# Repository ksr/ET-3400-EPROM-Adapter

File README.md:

# ET-3400-EPROM-Adapter

Adapter to replace original ROM in ET-3400 with a standard 2716 or 2732 EPROM

Using jumpers EPROM can be enabled in 1K blocks

USE V1.1

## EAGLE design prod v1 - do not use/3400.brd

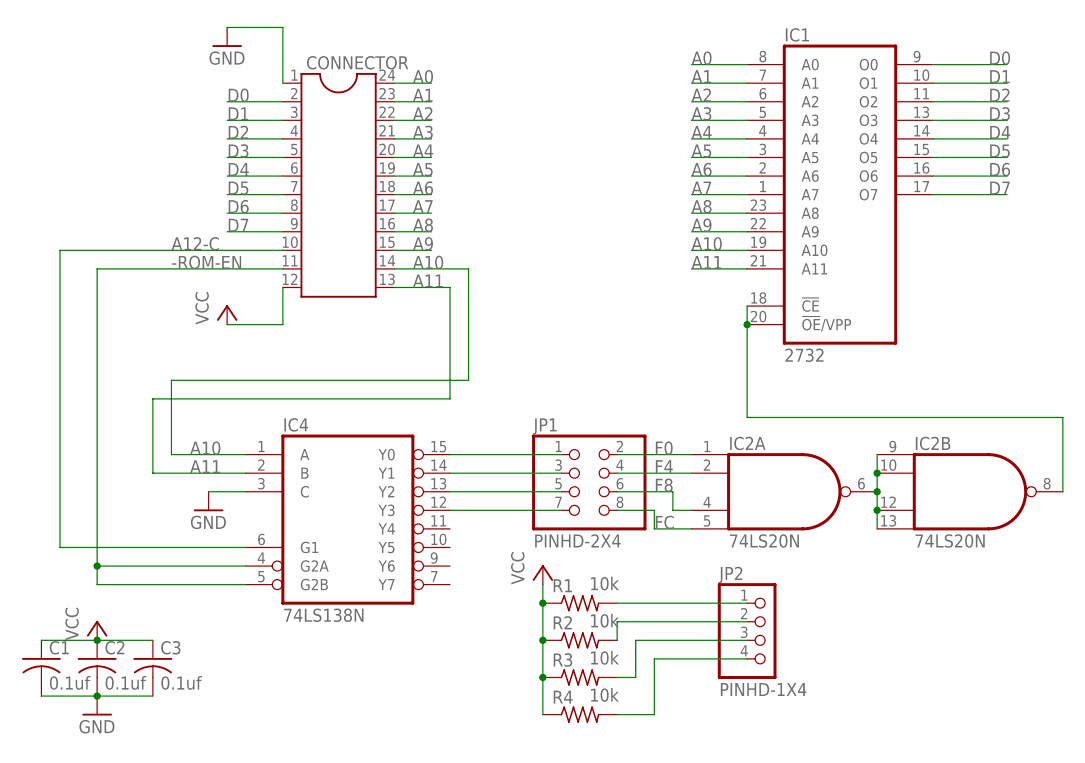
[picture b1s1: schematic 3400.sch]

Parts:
C1, C2, C3: 0.1uf; C025-024X044
CONNECTOR: DIL24-6
IC1: 2732; DIL24
IC2: 74LS20N; DIL14
IC4: 74LS138N; DIL16
JP1: PINHD-2X4; 2X04
JP2: PINHD-1X4; 1X04
R1, R2, R3, R4: 10k; 0207/10

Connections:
-ROM-EN: CONNECTOR.11, IC4.4 (G2A), IC4.5 (G2B)
A0: CONNECTOR.24, IC1.8 (A0)
A1: CONNECTOR.23, IC1.7 (A1)
A2: CONNECTOR.22, IC1.6 (A2)
A3: CONNECTOR.21, IC1.5 (A3)
A4: CONNECTOR.20, IC1.4 (A4)
A5: CONNECTOR.19, IC1.3 (A5)
A6: CONNECTOR.18, IC1.2 (A6)
A7: CONNECTOR.17, IC1.1 (A7)
A8: CONNECTOR.16, IC1.23 (A8)
A9: CONNECTOR.15, IC1.22 (A9)
A10: CONNECTOR.14, IC1.19 (A10), IC4.1 (A)
A11: CONNECTOR.13, IC1.21 (A11), IC4.2 (B)
A12-C: CONNECTOR.10, IC4.6 (G1)
D0: CONNECTOR.2, IC1.9 (O0)
D1: CONNECTOR.3, IC1.10 (O1)
D2: CONNECTOR.4, IC1.11 (O2)
D3: CONNECTOR.5, IC1.13 (O3)
D4: CONNECTOR.6, IC1.14 (O4)
D5: CONNECTOR.7, IC1.15 (O5)
D6: CONNECTOR.8, IC1.16 (O6)
D7: CONNECTOR.9, IC1.17 (O7)
F0: IC2.1 (I0), JP1.2
F4: IC2.2 (I1), JP1.4
F8: IC2.4 (I2), JP1.6
FC: IC2.5 (I3), JP1.8
GND: C1.2, C2.2, C3.2, CONNECTOR.1, IC1.12 (GND), IC2.7 (GND), IC4.3 (C), IC4.8 (GND)
unnamed: IC1.18 (!CE), IC1.20 (!OE!/VPP), IC2.8 (O)
unnamed: IC4.15 (Y0), JP1.1
unnamed: IC2.6 (O), IC2.9 (I0), IC2.10 (I1), IC2.12 (I2), IC2.13 (I3)
unnamed: IC4.14 (Y1), JP1.3
unnamed: IC4.13 (Y2), JP1.5
unnamed: IC4.12 (Y3), JP1.7
unnamed: JP2.1, R1.2
unnamed: JP2.2, R2.2
unnamed: JP2.3, R3.2
unnamed: JP2.4, R4.2
VCC: C1.1, C2.1, C3.1, CONNECTOR.12, IC1.24 (VCC), IC2.14 (VCC), IC4.16 (VCC), R1.1, R2.1, R3.1, R4.1

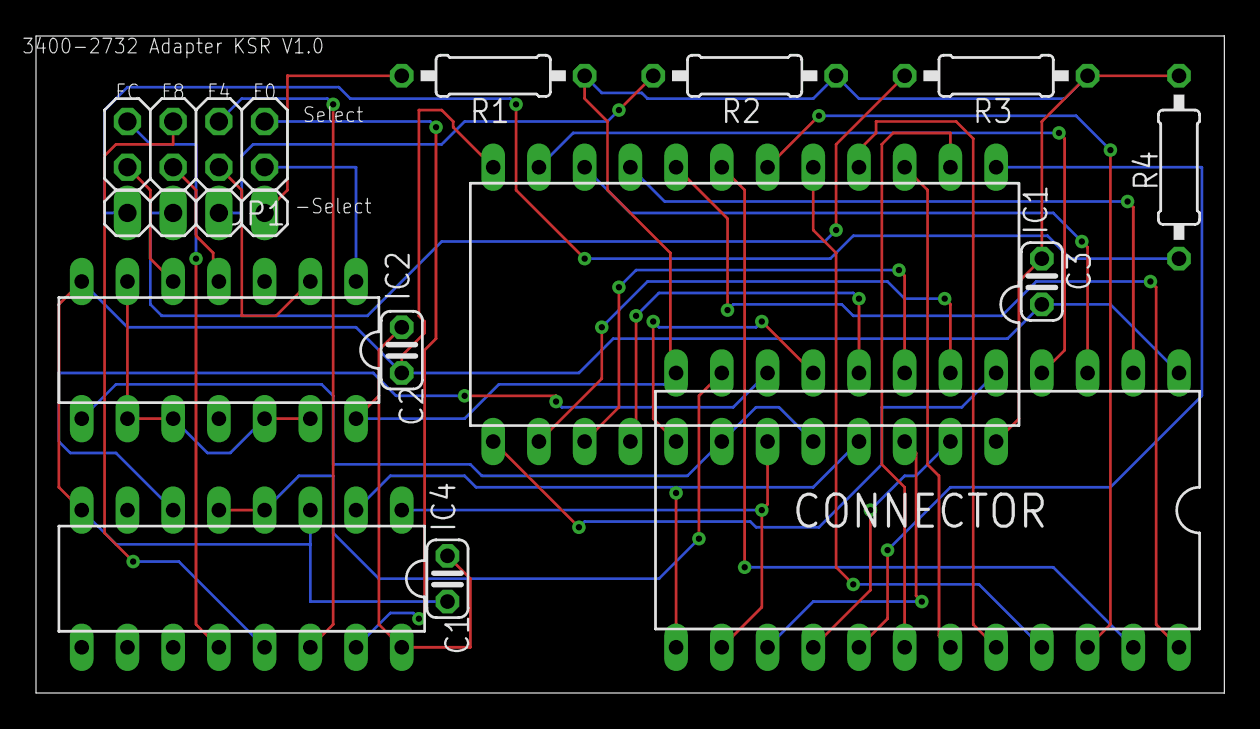
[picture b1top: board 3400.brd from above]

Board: 2 copper layers, 66.0 x 36.5 mm, 13 parts (0 on the bottom side), 38 nets.

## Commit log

2020-12-26 Initial Checkin - USE V1.1
2020-12-26 Added images
2021-01-01 adding PDFs of schematic and brd file
2021-01-01 add do not use info
